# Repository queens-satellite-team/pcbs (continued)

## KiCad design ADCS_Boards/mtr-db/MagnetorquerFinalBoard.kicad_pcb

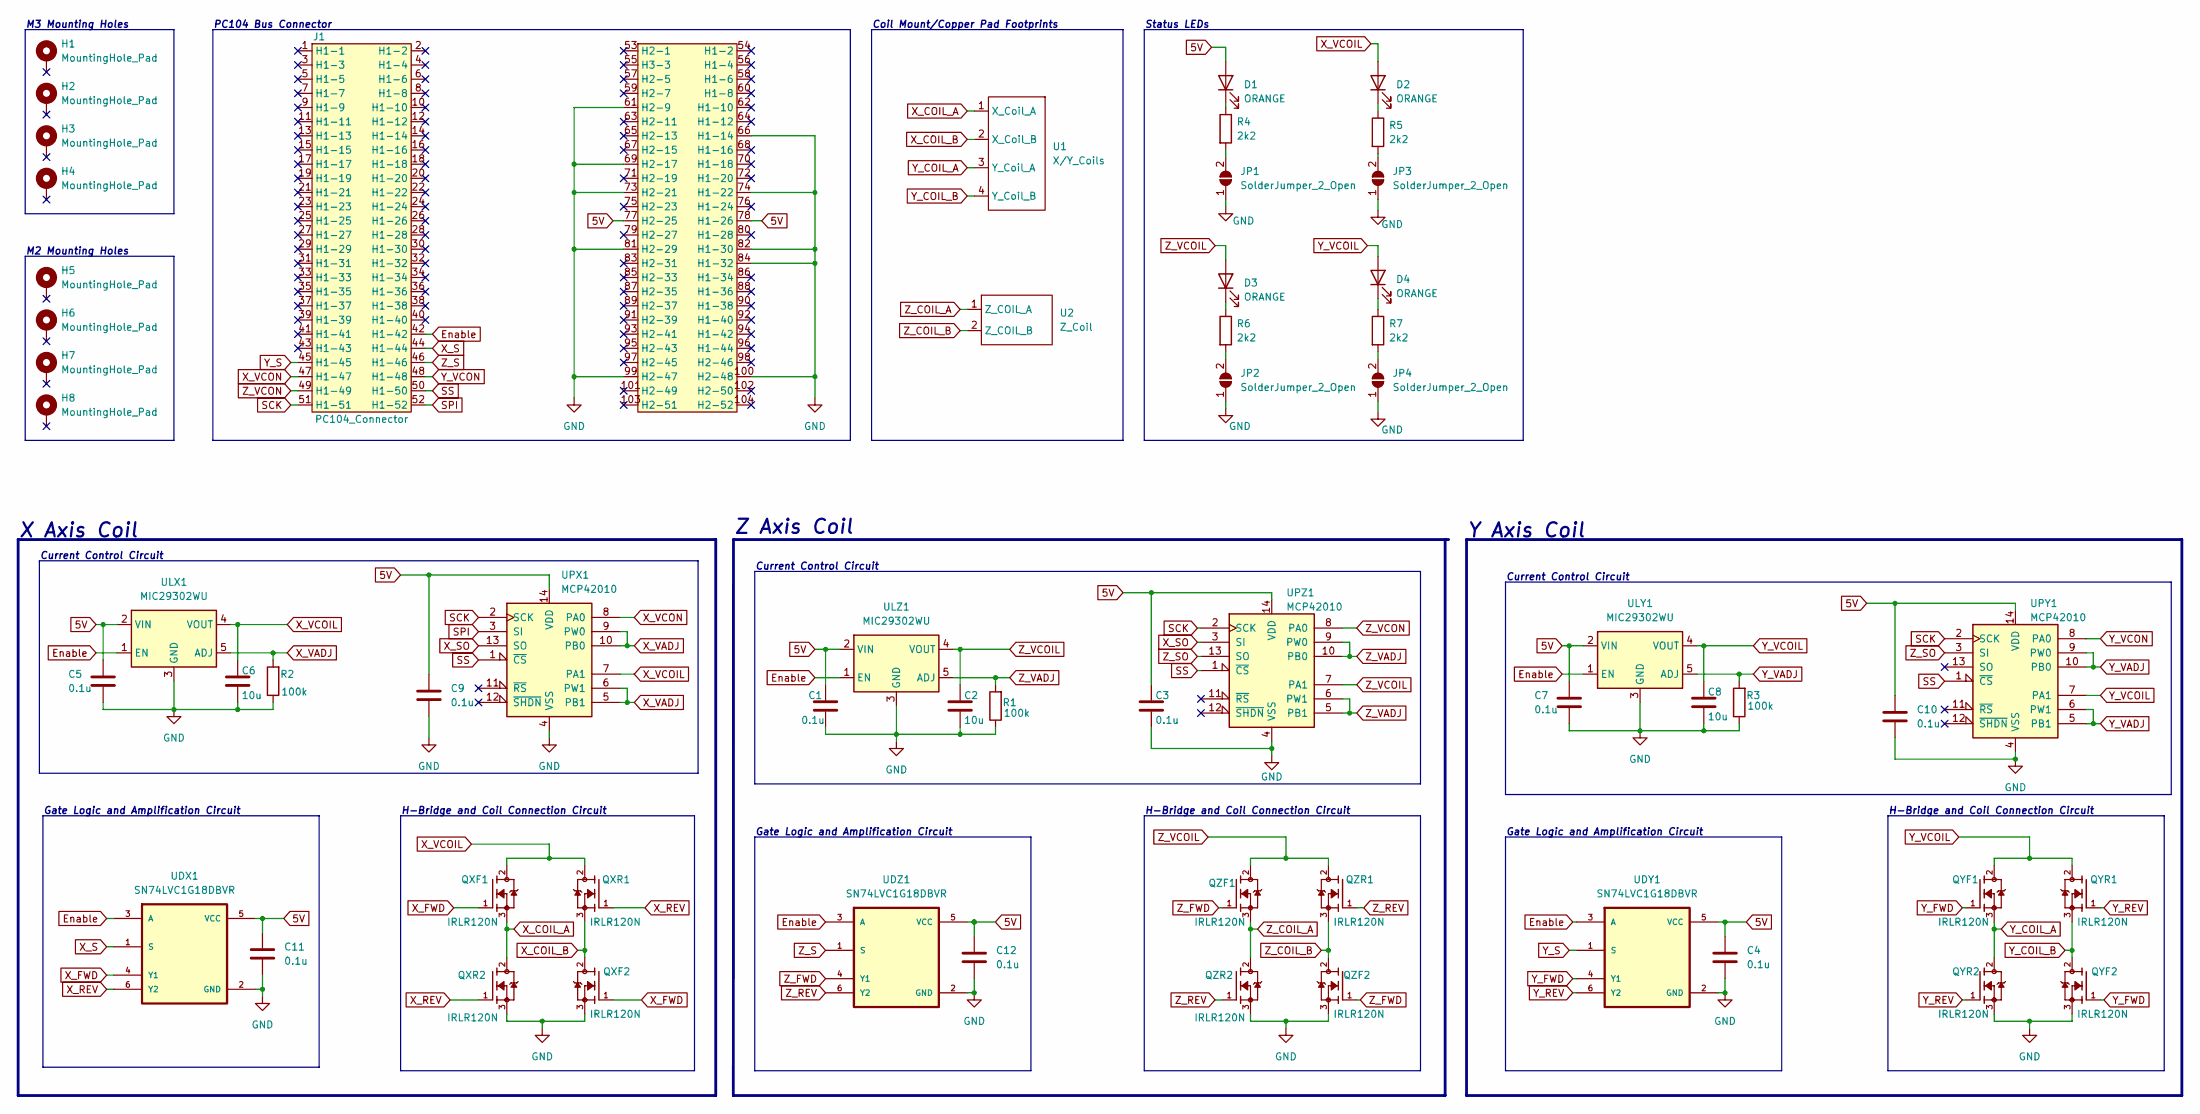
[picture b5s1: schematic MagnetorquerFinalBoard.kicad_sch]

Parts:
C1, C3, C4, C5, C7, C9, C10, C11, C12: 0.1u; C_0603_1608Metric
C2, C6, C8: 10u; C_0603_1608Metric
D1, D2, D3, D4: ORANGE; LED_0603_1608Metric
H1, H2, H3, H4: MountingHole_Pad; MountingHole_3.2mm_M3_Pad_TopBottom
H5, H6, H7, H8: MountingHole_Pad; MountingHole_2.2mm_M2_Pad_TopBottom
J1: PC104_Connector; pc104-connector
JP1, JP2, JP3, JP4: SolderJumper_2_Open; SolderJumper-2_P1.3mm_Open_TrianglePad1.0x1.5mm
QXF1, QXF2: IRLR120N; TO-252-2; PARTREV july 2014
QXR1, QXR2: IRLR120N; TO-252-2; PARTREV july 2014
QYF1, QYF2: IRLR120N; TO-252-2; PARTREV july 2014
QYR1, QYR2: IRLR120N; TO-252-2; PARTREV july 2014
QZF1, QZF2: IRLR120N; TO-252-2; PARTREV july 2014
QZR1, QZR2: IRLR120N; TO-252-2; PARTREV july 2014
R1, R2, R3: 100k; R_0603_1608Metric
R4, R5, R6, R7: 2k2; R_0603_1608Metric
U1: X/Y_Coils; Front Coils Mount
U2: Z_Coil; ZCoil
UDX1: SN74LVC1G18DBVR; SOT95P280X145-6N
UDY1: SN74LVC1G18DBVR; SOT95P280X145-6N
UDZ1: SN74LVC1G18DBVR; SOT95P280X145-6N
ULX1: MIC29302WU; TO-263-5_TabPin3
ULY1: MIC29302WU; TO-263-5_TabPin3
ULZ1: MIC29302WU; TO-263-5_TabPin3
UPX1: MCP42010; SOIC127P600X175-14N
UPY1: MCP42010; SOIC127P600X175-14N
UPZ1: MCP42010; SOIC127P600X175-14N

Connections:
5V: C1.1, C3.1, C4.1, C5.1, C7.1, C9.1, C10.1, C11.1, C12.1, D1.2 (A), J1.77 (H2-25), J1.78 (H1-26), UDX1.5 (VCC), UDY1.5 (VCC), UDZ1.5 (VCC), ULX1.2 (VIN), ULY1.2 (VIN), ULZ1.2 (VIN), UPX1.14 (VDD), UPY1.14 (VDD), UPZ1.14 (VDD)
Enable: J1.42 (H1-42), UDX1.3 (A), UDY1.3 (A), UDZ1.3 (A), ULX1.1 (EN), ULY1.1 (EN), ULZ1.1 (EN)
GND: C1.2, C2.2, C3.2, C4.2, C5.2, C6.2, C7.2, C8.2, C9.2, C10.2, C11.2, C12.2, J1.61 (H2-9), J1.66 (H1-14), J1.69 (H2-17), J1.73 (H2-21), J1.74 (H1-22), J1.81 (H2-29), J1.82 (H1-30), J1.84 (H1-32), J1.99 (H2-47), J1.100 (H2-48), JP1.1 (A), JP2.1 (A), JP3.1 (A), JP4.1 (A), QXF2.3, QXR2.3, QYF2.3, QYR2.3, QZF2.3, QZR2.3, R1.1, R2.1, R3.1, UDX1.2 (GND), UDY1.2 (GND), UDZ1.2 (GND), ULX1.3 (GND), ULY1.3 (GND), ULZ1.3 (GND), UPX1.4 (VSS), UPY1.4 (VSS), UPZ1.4 (VSS)
unnamed: D1.1 (K), R4.1
unnamed: D2.1 (K), R5.1
unnamed: D3.1 (K), R6.1
unnamed: D4.1 (K), R7.1
unnamed: JP1.2 (B), R4.2
unnamed: JP3.2 (B), R5.2
unnamed: JP2.2 (B), R6.2
unnamed: JP4.2 (B), R7.2
SCK: J1.51 (H1-51), UPX1.2 (SCK), UPY1.2 (SCK), UPZ1.2 (SCK)
SPI: J1.52 (H1-52), UPX1.3 (SI)
SS: J1.50 (H1-50), UPX1.1 (~CS), UPY1.1 (~CS), UPZ1.1 (~CS)
X_COIL_A: QXF1.3, QXR2.2, U1.1 (X_Coil_A)
X_COIL_B: QXF2.2, QXR1.3, U1.2 (X_Coil_B)
X_FWD: QXF1.1, QXF2.1, UDX1.4 (Y1)
X_REV: QXR1.1, QXR2.1, UDX1.6 (Y2)
X_S: J1.44 (H1-44), UDX1.1 (S)
X_SO: UPX1.13 (SO), UPZ1.3 (SI)
X_VADJ: R2.2, ULX1.5 (ADJ), UPX1.5 (PB1), UPX1.6 (PW1), UPX1.9 (PW0), UPX1.10 (PB0)
X_VCOIL: C6.1, D2.2 (A), QXF1.2, QXR1.2, ULX1.4 (VOUT), UPX1.7 (PA1)
X_VCON: J1.47 (H1-47), UPX1.8 (PA0)
Y_COIL_A: QYF1.3, QYR2.2, U1.3 (Y_Coil_A)
Y_COIL_B: QYF2.2, QYR1.3, U1.4 (Y_Coil_B)
Y_FWD: QYF1.1, QYF2.1, UDY1.4 (Y1)
Y_REV: QYR1.1, QYR2.1, UDY1.6 (Y2)
Y_S: J1.45 (H1-45), UDY1.1 (S)
Y_VADJ: R3.2, ULY1.5 (ADJ), UPY1.5 (PB1), UPY1.6 (PW1), UPY1.9 (PW0), UPY1.10 (PB0)
Y_VCOIL: C8.1, D4.2 (A), QYF1.2, QYR1.2, ULY1.4 (VOUT), UPY1.7 (PA1)
Y_VCON: J1.48 (H1-48), UPY1.8 (PA0)
Z_COIL_A: QZF1.3, QZR2.2, U2.1 (Z_COIL_A)
Z_COIL_B: QZF2.2, QZR1.3, U2.2 (Z_COIL_B)
Z_FWD: QZF1.1, QZF2.1, UDZ1.4 (Y1)
Z_REV: QZR1.1, QZR2.1, UDZ1.6 (Y2)
Z_S: J1.46 (H1-46), UDZ1.1 (S)
Z_SO: UPY1.3 (SI), UPZ1.13 (SO)
Z_VADJ: R1.2, ULZ1.5 (ADJ), UPZ1.5 (PB1), UPZ1.6 (PW1), UPZ1.9 (PW0), UPZ1.10 (PB0)
Z_VCOIL: C2.1, D3.2 (A), QZF1.2, QZR1.2, ULZ1.4 (VOUT), UPZ1.7 (PA1)
Z_VCON: J1.49 (H1-49), UPZ1.8 (PA0)

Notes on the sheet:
M3 Mounting Holes
Gate Logic and Amplification Circuit
M2 Mounting Holes
Status LEDs
Z Axis Coil
X Axis Coil
Current Control Circuit
Y Axis Coil
PC104 Bus Connector
H-Bridge and Coil Connection Circuit
Coil Mount/Copper Pad Footprints

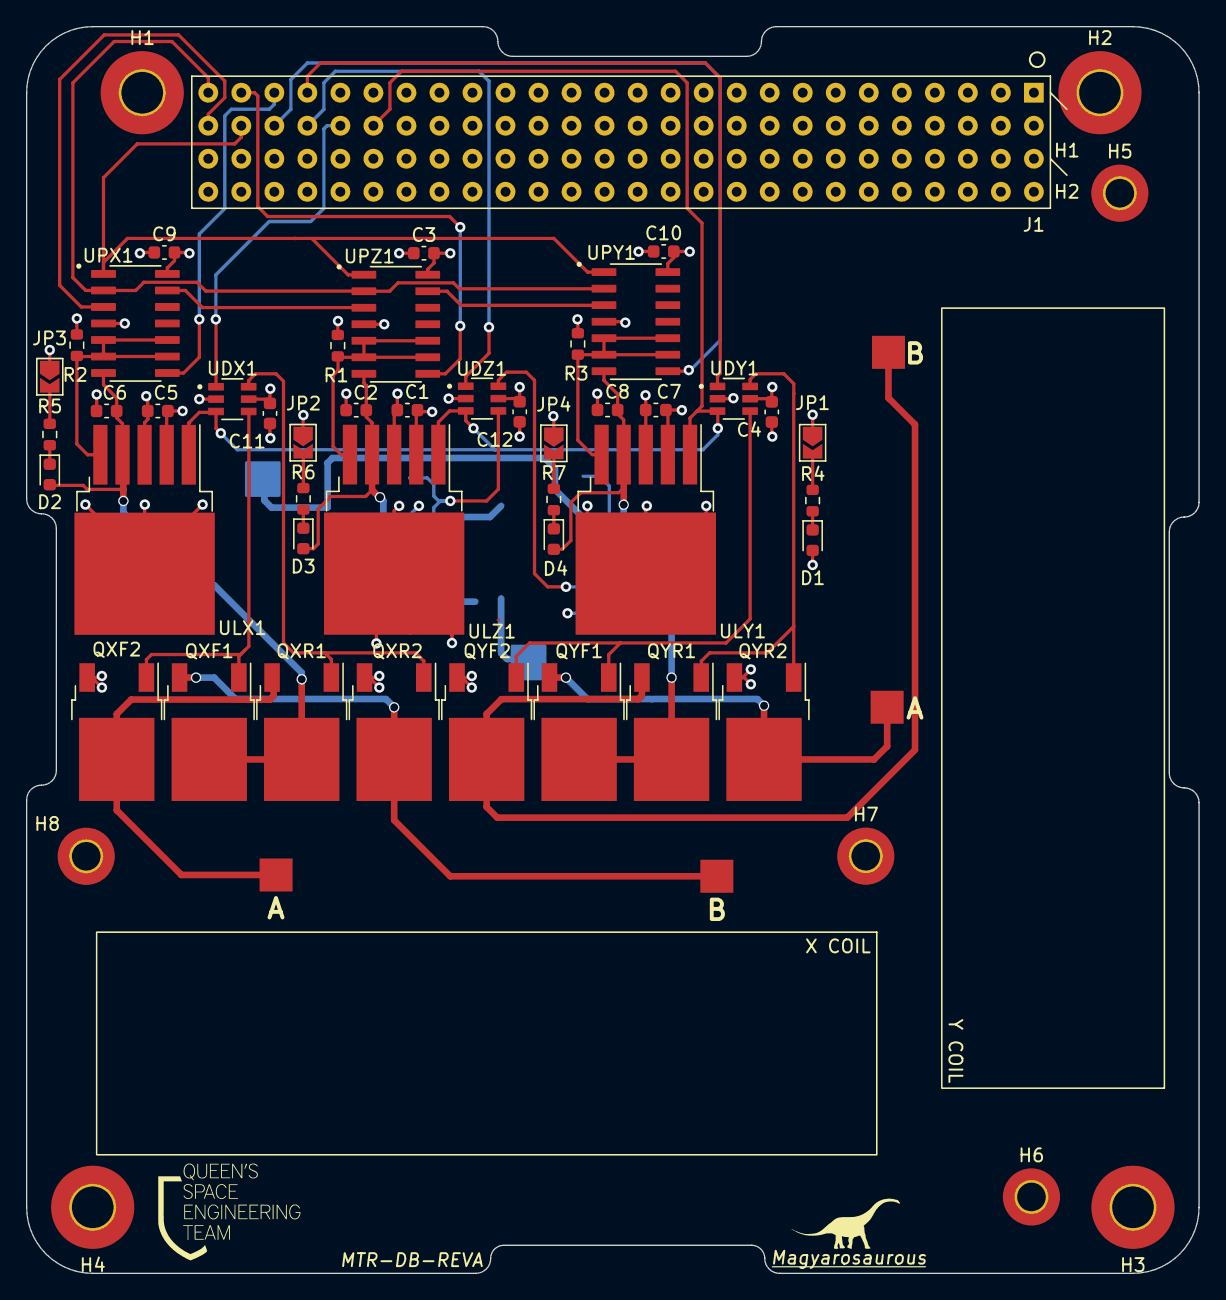
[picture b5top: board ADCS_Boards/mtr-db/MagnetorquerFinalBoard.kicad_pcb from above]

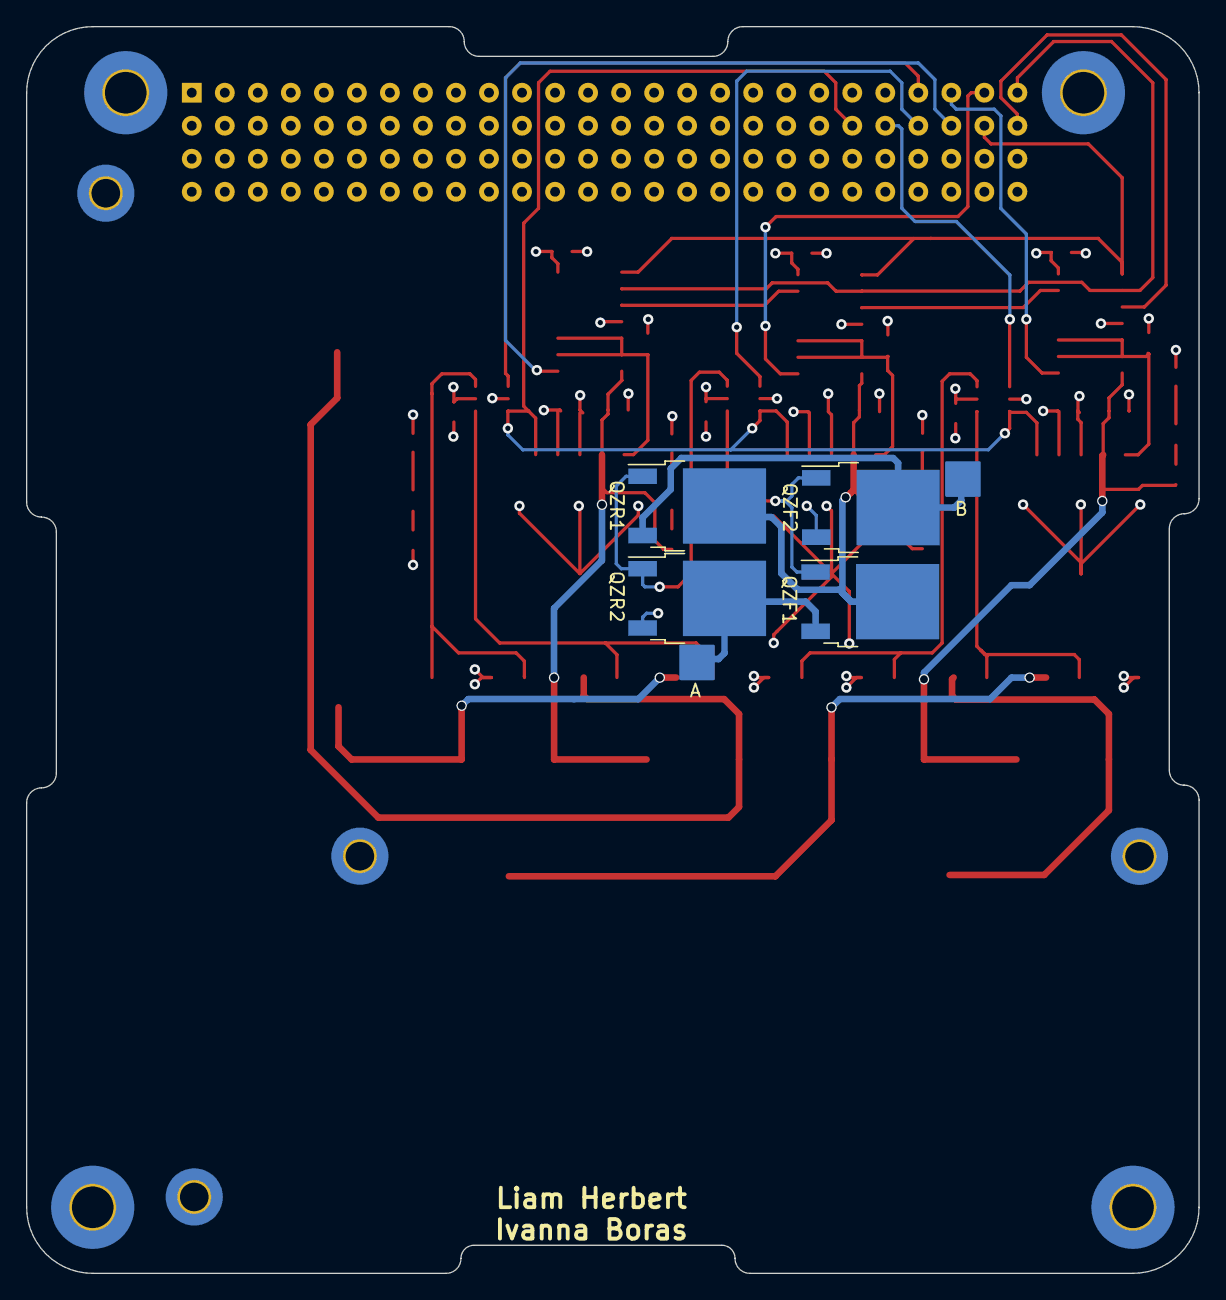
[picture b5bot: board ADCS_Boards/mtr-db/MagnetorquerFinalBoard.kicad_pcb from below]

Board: 4 copper layers, 90.2 x 95.9 mm, 58 parts (4 on the bottom side), 40 nets.

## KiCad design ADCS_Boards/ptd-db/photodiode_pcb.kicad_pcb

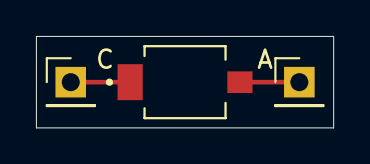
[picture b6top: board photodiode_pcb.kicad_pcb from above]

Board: 2 copper layers, 16.5 x 5.1 mm, 3 parts (0 on the bottom side), 2 nets.

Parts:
A: Conn_01x01; PinHeader_1x01_P2.54mm_Vertical
C: Conn_01x01; PinHeader_1x01_P2.54mm_Vertical
D1: SFH_2430-Z; DIO_SFH_2430-Z

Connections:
unnamed: A.1, D1.A
unnamed: C.1, D1.C
